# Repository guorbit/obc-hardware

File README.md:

# STM32-based Onboard Computer

This repository contains the KiCad project files and fabrication outputs of GU Orbit's new generation STM32F4-based OBC board.

Revision A of this board will fly on the CloudView-2 high altitude balloon mission. This revision is an 100% COTS design with no space grade parts.

## Documentation

### User Manual

Available [HERE](https://gla.sharepoint.com/:w:/s/GUorbit/EWbB4_OCiA1IiK20_8yILmEBxFCxNbRzXe-6b-aP8d8sqQ?e=ERlZXE) (University of Glasgow login required)

### Schematic Diagram

Available [HERE](https://gla.sharepoint.com/:b:/s/GUorbit/EcqzIoVTQb1NrapEKPAgqEgBkPuZpGcCXpksztv5thLR0g?e=U3XVNj) (University of Glasgow login required)

### Mechanical Drawing

Available [HERE](https://gla.sharepoint.com/:b:/s/GUorbit/EUr8ayuSMrpKpmlO9UEF-kwB01D8GUk2koGHjnPf7s4Tdw?e=q49YmD) (University of Glasgow login required)

### 3D Model for CAD

Available under the [CAD](/CAD) directory in STEP and FreeCAD formats

## Next Revision TODOs

- [ ] Replace HSE, LSE crystals with TCXO for precision
- [ ] Use another LTC4411 to protect the SWD port

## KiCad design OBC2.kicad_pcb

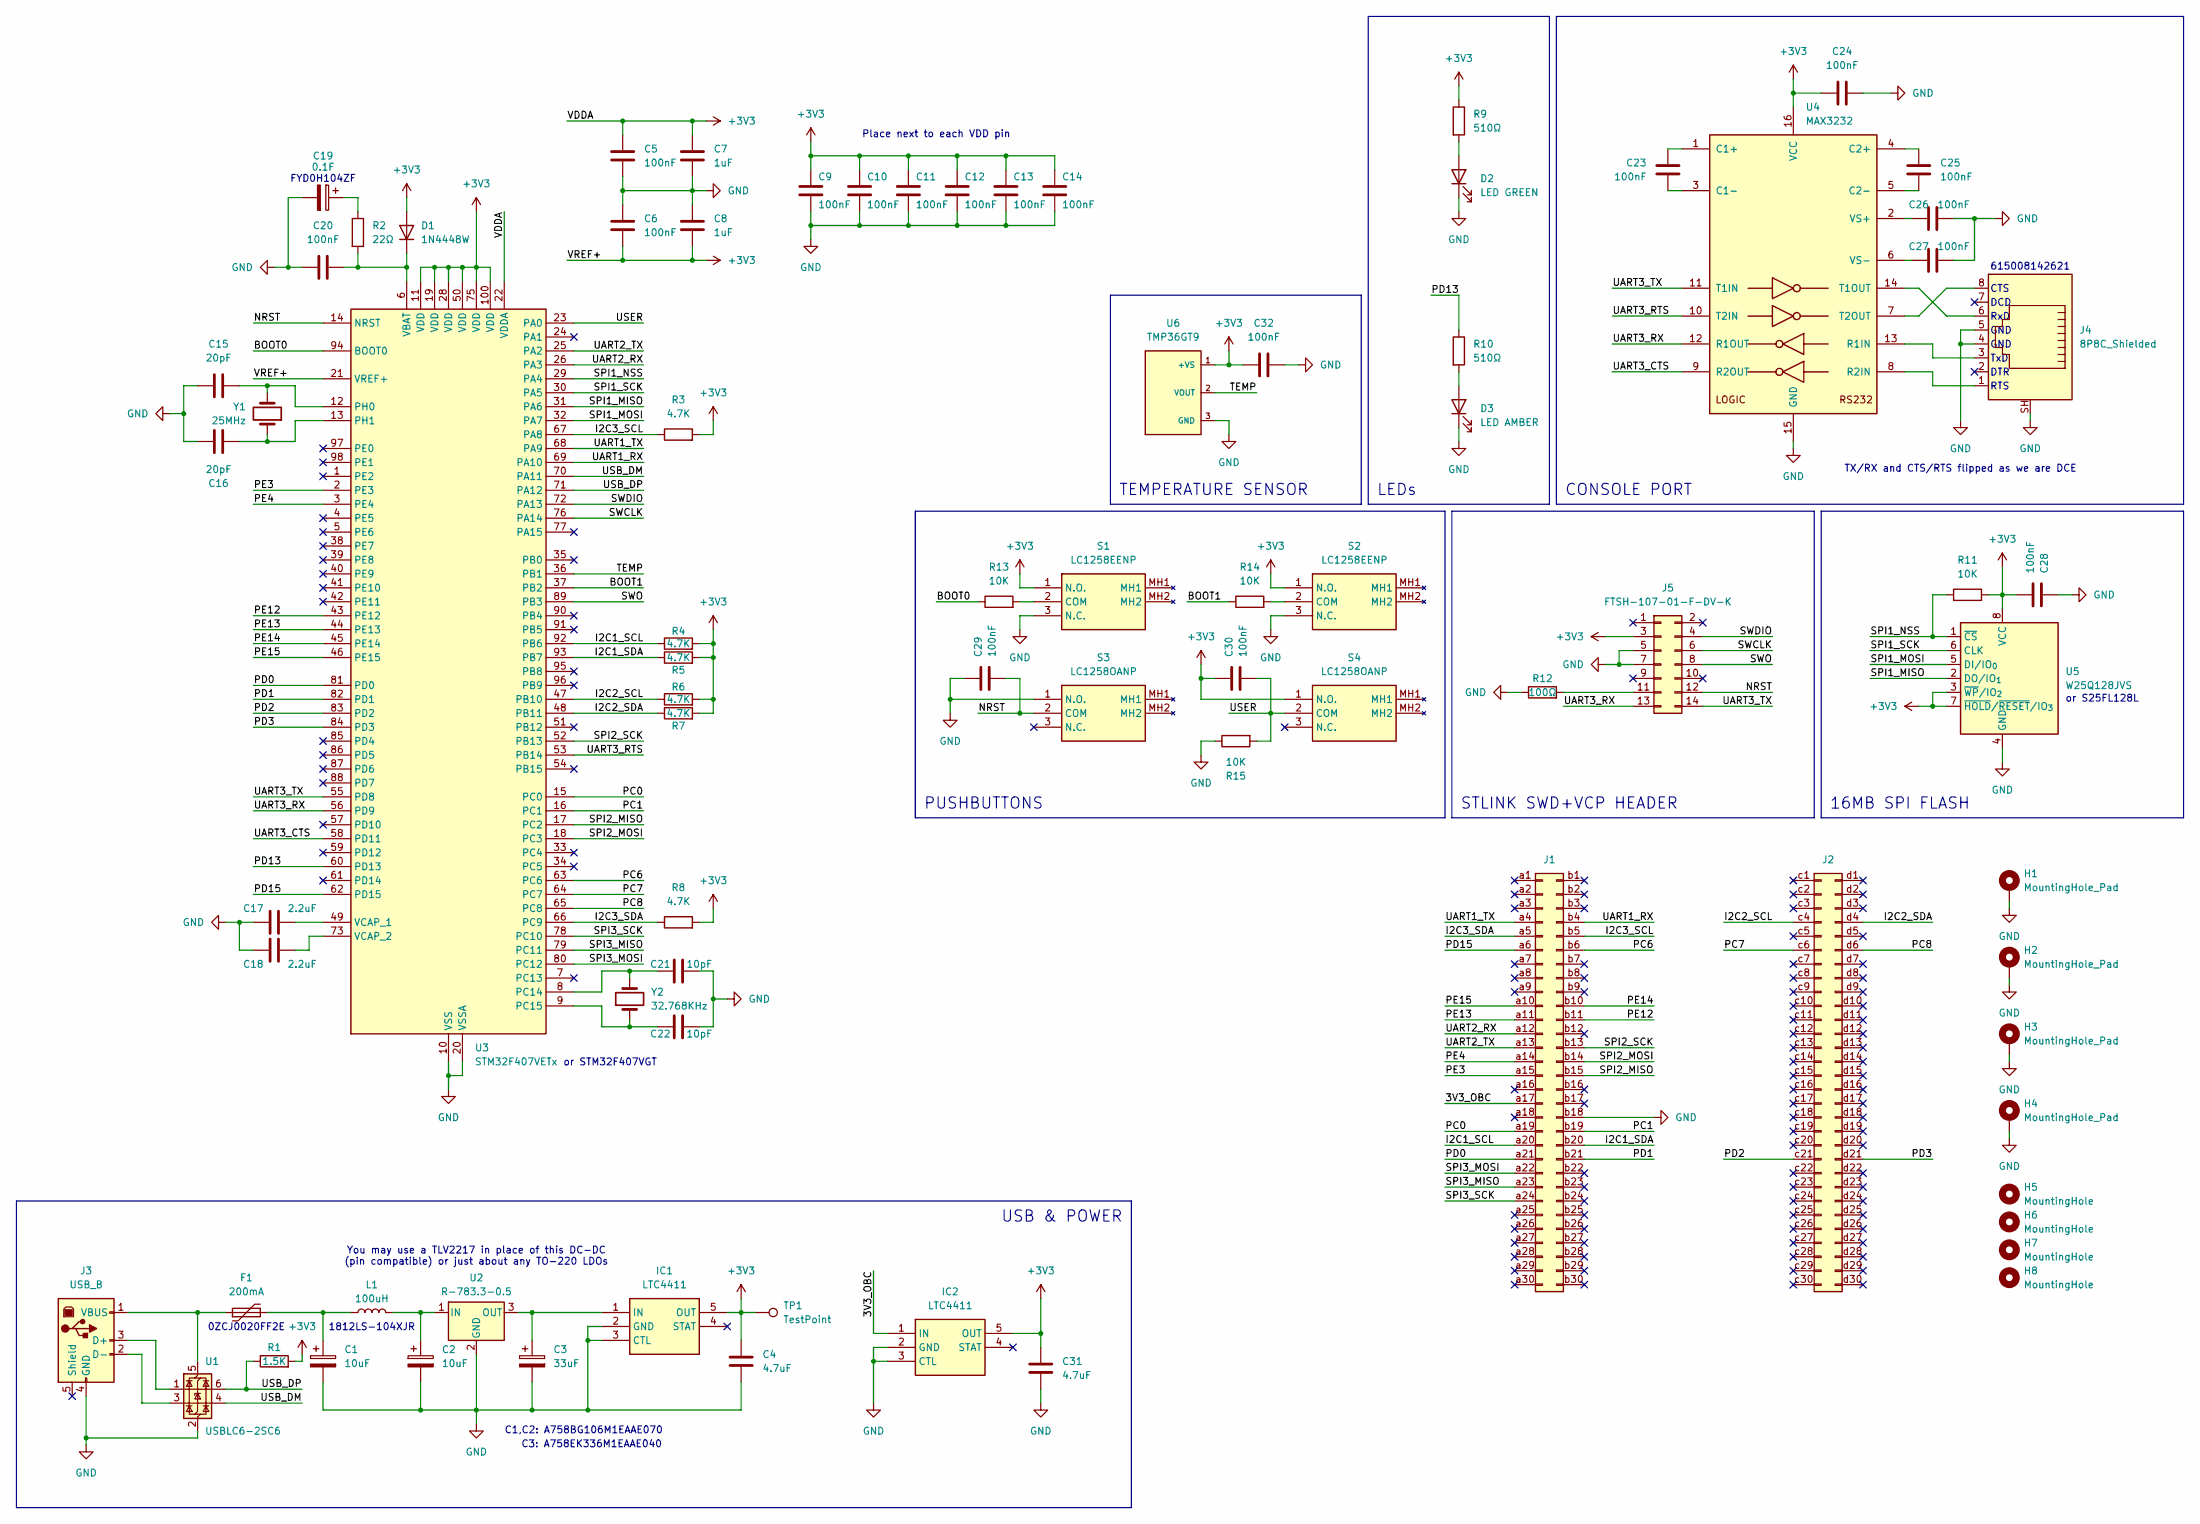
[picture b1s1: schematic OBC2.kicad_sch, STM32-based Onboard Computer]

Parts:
C1, C2: 10uF; CP_Radial_D5.0mm_P2.00mm
C3: 33uF; CP_Radial_D6.3mm_P2.50mm
C4, C31: 4.7uF; C_1206_3216Metric
C5, C6, C9, C10, C11, C12, C13, C14, C20, C23, C24, C25, C26, C27, C28, C29, C30, C32: 100nF; C_1206_3216Metric
C7, C8: 1uF; C_1206_3216Metric
C15, C16: 20pF; C_1206_3216Metric
C17, C18: 2.2uF; C_1206_3216Metric
C19: 0.1F; CP_Radial_D13.0mm_P5.00mm
C21, C22: 10pF; C_1206_3216Metric
D1: 1N4448W; D_SOD-123
D2: LED GREEN; LED_D5.0mm_Horizontal_O3.81mm_Z3.0mm
D3: LED AMBER; LED_D5.0mm_Horizontal_O3.81mm_Z3.0mm
F1: 200mA; Fuse_1206_3216Metric
H1, H2, H3, H4: MountingHole_Pad; MountingHole_3.2mm_M3_Pad_TopBottom
H5, H6, H7, H8: MountingHole; MountingHole_2mm
IC1, IC2: LTC4411; TSOT-23-5; Manufacturer_Part_Number LTC4411ES5#TRMPBF
J1, J2: Conn_02x30_Row_Letter_First; PinSocket_2x30_P2.00mm_Vertical
J3: USB_B; USB_B_Lumberg_2411_02_Horizontal
J4: 8P8C_Shielded; RJ45_Wuerth_7499010001A_Horizontal
J5: FTSH-107-01-F-DV-K; PinHeader_2x07_P1.27mm_Vertical_SMD
L1: 100uH; L_1812_4532Metric
R1: 1.5K; R_1206_3216Metric
R2: 22Ω; R_1206_3216Metric
R3, R4, R5, R6, R7, R8: 4.7K; R_1206_3216Metric
R9, R10: 510Ω; R_1206_3216Metric
R11, R13, R14, R15: 10K; R_1206_3216Metric
R12: 100Ω; R_1206_3216Metric
S1, S2: LC1258EENP; Manufacturer_Part_Number LC1258EENP; Mouser Part Number 612-LC1258EENP
S3, S4: LC1258OANP; Manufacturer_Part_Number LC1258OANP; Mouser Part Number 612-LC1258OANP
TP1: TestPoint; TestPoint_Loop_D2.60mm_Drill1.6mm_Beaded
U1: USBLC6-2SC6; SOT-23-6
U2: R-783.3-0.5; Converter_DCDC_RECOM_R-78E-0.5_THT
U3: STM32F407VETx; LQFP-100_14x14mm_P0.5mm
U4: MAX3232; SOIC-16_3.9x9.9mm_P1.27mm
U5: W25Q128JVS; SOIC-8_5.3x5.3mm_P1.27mm
U6: TMP36GT9; TO-92_Inline; PARTREV H
Y1: 25MHz; Crystal_SMD_HC49-SD
Y2: 32.768KHz; Crystal_C38-LF_D3.0mm_L8.0mm_Horizontal

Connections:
+3V3: C4.2, C5.2, C6.1, C7.2, C8.1, C9.2, C10.2, C11.2, C12.2, C13.2, C14.2, C24.1, C28.1, C30.1, C31.2, C32.1, D1.2 (A), IC1.5 (OUT), IC2.5 (OUT), J5.3, R1.2, R3.2, R4.2, R5.2, R6.2, R7.2, R8.2, R9.1, R11.2, S1.1 (N.O.), S2.1 (N.O.), S4.1 (N.O.), TP1.1, U3.11 (VDD), U3.19 (VDD), U3.21 (VREF+), U3.22 (VDDA), U3.28 (VDD), U3.50 (VDD), U3.75 (VDD), U3.100 (VDD), U4.16 (VCC), U5.3 (~WP/IO_{2}), U5.7 (~HOLD/~RESET/IO_{3}), U5.8 (VCC), U6.1 (+VS)
/3V3_OBC: IC2.1 (IN), J1.a17
/BOOT0: R13.1, U3.94 (BOOT0)
/BOOT1: R14.1, U3.37 (PB2)
/I2C1_SCL: J1.a20, R4.1, U3.92 (PB6)
/I2C1_SDA: J1.b20, R5.1, U3.93 (PB7)
/I2C2_SCL: J2.c4 (Pin_a4), R6.1, U3.47 (PB10)
/I2C2_SDA: J2.d4 (Pin_b4), R7.1, U3.48 (PB11)
/I2C3_SCL: J1.b5, R3.1, U3.67 (PA8)
/I2C3_SDA: J1.a5, R8.1, U3.66 (PC9)
/NRST: C29.2, J5.12, S3.2 (COM), U3.14 (NRST)
/PC0: J1.a19, U3.15 (PC0)
/PC1: J1.b19, U3.16 (PC1)
/PC6: J1.b6, U3.63 (PC6)
/PC7: J2.c6 (Pin_a6), U3.64 (PC7)
/PC8: J2.d6 (Pin_b6), U3.65 (PC8)
/PD0: J1.a21, U3.81 (PD0)
/PD1: J1.b21, U3.82 (PD1)
/PD2: J2.c21 (Pin_a21), U3.83 (PD2)
/PD3: J2.d21 (Pin_b21), U3.84 (PD3)
/PD13: R10.1, U3.60 (PD13)
/PD15: J1.a6, U3.62 (PD15)
/PE3: J1.a15, U3.2 (PE3)
/PE4: J1.a14, U3.3 (PE4)
/PE12: J1.b11, U3.43 (PE12)
/PE13: J1.a11, U3.44 (PE13)
/PE14: J1.b10, U3.45 (PE14)
/PE15: J1.a10, U3.46 (PE15)
/SPI1_MISO: U3.31 (PA6), U5.2 (DO/IO_{1})
/SPI1_MOSI: U3.32 (PA7), U5.5 (DI/IO_{0})
/SPI1_NSS: R11.1, U3.29 (PA4), U5.1 (~CS)
/SPI1_SCK: U3.30 (PA5), U5.6 (CLK)
/SPI2_MISO: J1.b15, U3.17 (PC2)
/SPI2_MOSI: J1.b14, U3.18 (PC3)
/SPI2_SCK: J1.b13, U3.52 (PB13)
/SPI3_MISO: J1.a23, U3.79 (PC11)
/SPI3_MOSI: J1.a22, U3.80 (PC12)
/SPI3_SCK: J1.a24, U3.78 (PC10)
/SWCLK: J5.6, U3.76 (PA14)
/SWDIO: J5.4, U3.72 (PA13)
/SWO: J5.8, U3.89 (PB3)
/TEMP: U3.36 (PB1), U6.2 (VOUT)
/UART1_RX: J1.b4, U3.69 (PA10)
/UART1_TX: J1.a4, U3.68 (PA9)
/UART2_RX: J1.a12, U3.26 (PA3)
/UART2_TX: J1.a13, U3.25 (PA2)
/UART3_CTS: U3.58 (PD11), U4.9 (R2OUT)
/UART3_RTS: U3.53 (PB14), U4.10 (T2IN)
/UART3_RX: J5.13, U3.56 (PD9), U4.12 (R1OUT)
/UART3_TX: J5.14, U3.55 (PD8), U4.11 (T1IN)
/USB_DM: U1.4 (I/O2), U3.70 (PA11)
/USB_DP: R1.1, U1.6 (I/O1), U3.71 (PA12)
/USER: C30.2, R15.2, S4.2 (COM), U3.23 (PA0)
GND: C1.2, C2.2, C3.2, C4.1, C5.1, C6.2, C7.1, C8.2, C9.1, C10.1, C11.1, C12.1, C13.1, C14.1, C15.1, C16.1, C17.1, C18.1, C19.2, C20.1, C21.2, C22.2, C24.2, C26.1, C27.1, C28.2, C29.1, C31.1, C32.2, D2.1 (K), D3.1 (K), H1.1, H2.1, H3.1, H4.1, IC1.2 (GND), IC1.3 (CTL), IC2.2 (GND), IC2.3 (CTL), J1.b18, J3.4 (GND), J4.4, J4.5, J4.SH, J5.5, J5.7, R12.1, R15.1, S1.3 (N.C.), S2.3 (N.C.), S3.1 (N.O.), U1.2 (GND), U2.2 (GND), U3.10 (VSS), U3.20 (VSSA), U3.27 (VSS), U3.74 (VSS), U3.99 (VSS), U4.15 (GND), U5.4 (GND), U6.3 (GND)
unnamed: C1.1, F1.2, L1.1
unnamed: C19.1, R2.1
unnamed: C20.2, D1.1 (K), R2.2, U3.6 (VBAT)
unnamed: D2.2 (A), R9.2
unnamed: D3.2 (A), R10.2
unnamed: C3.1, IC1.1 (IN), U2.3 (OUT)
unnamed: J3.3 (D+), U1.1 (I/O1)
unnamed: J3.2 (D-), U1.3 (I/O2)
unnamed: F1.1, J3.1 (VBUS), U1.5 (VBUS)
unnamed: J5.11, R12.2
unnamed: R13.2, S1.2 (COM)
unnamed: R14.2, S2.2 (COM)
unnamed: C2.1, L1.2, U2.1 (IN)
unnamed: C21.1, U3.8 (PC14), Y2.2
unnamed: C22.1, U3.9 (PC15), Y2.1
unnamed: C15.2, U3.12 (PH0), Y1.2
unnamed: C16.2, U3.13 (PH1), Y1.1
unnamed: C17.2, U3.49 (VCAP_1)
unnamed: C18.2, U3.73 (VCAP_2)
unnamed: C23.2, U4.1 (C1+)
unnamed: C23.1, U4.3 (C1-)
unnamed: C25.2, U4.4 (C2+)
unnamed: C25.1, U4.5 (C2-)
unnamed: J4.3, U4.13 (R1IN)
unnamed: J4.1, U4.8 (R2IN)
unnamed: J4.6, U4.14 (T1OUT)
unnamed: J4.8, U4.7 (T2OUT)
unnamed: C26.2, U4.2 (VS+)
unnamed: C27.2, U4.6 (VS-)

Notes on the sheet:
GND
FYD0H104ZF
or S25FL128L
CTS
RTS
TxD
C3: A758EK336M1EAAE040
Place next to each VDD pin
RxD
C1,C2: A758BG106M1EAAE070
You may use a TLV2217 in place of this DC-DC (pin compatible) or just about any TO-220 LDOs
or STM32F407VGT
615008142621
0ZCJ0020FF2E
DTR
TX/RX and CTS/RTS flipped as we are DCE
1812LS-104XJR
DCD
PUSHBUTTONS
USB & POWER
STLINK SWD+VCP HEADER
CONSOLE PORT
LEDs
TEMPERATURE SENSOR
16MB SPI FLASH

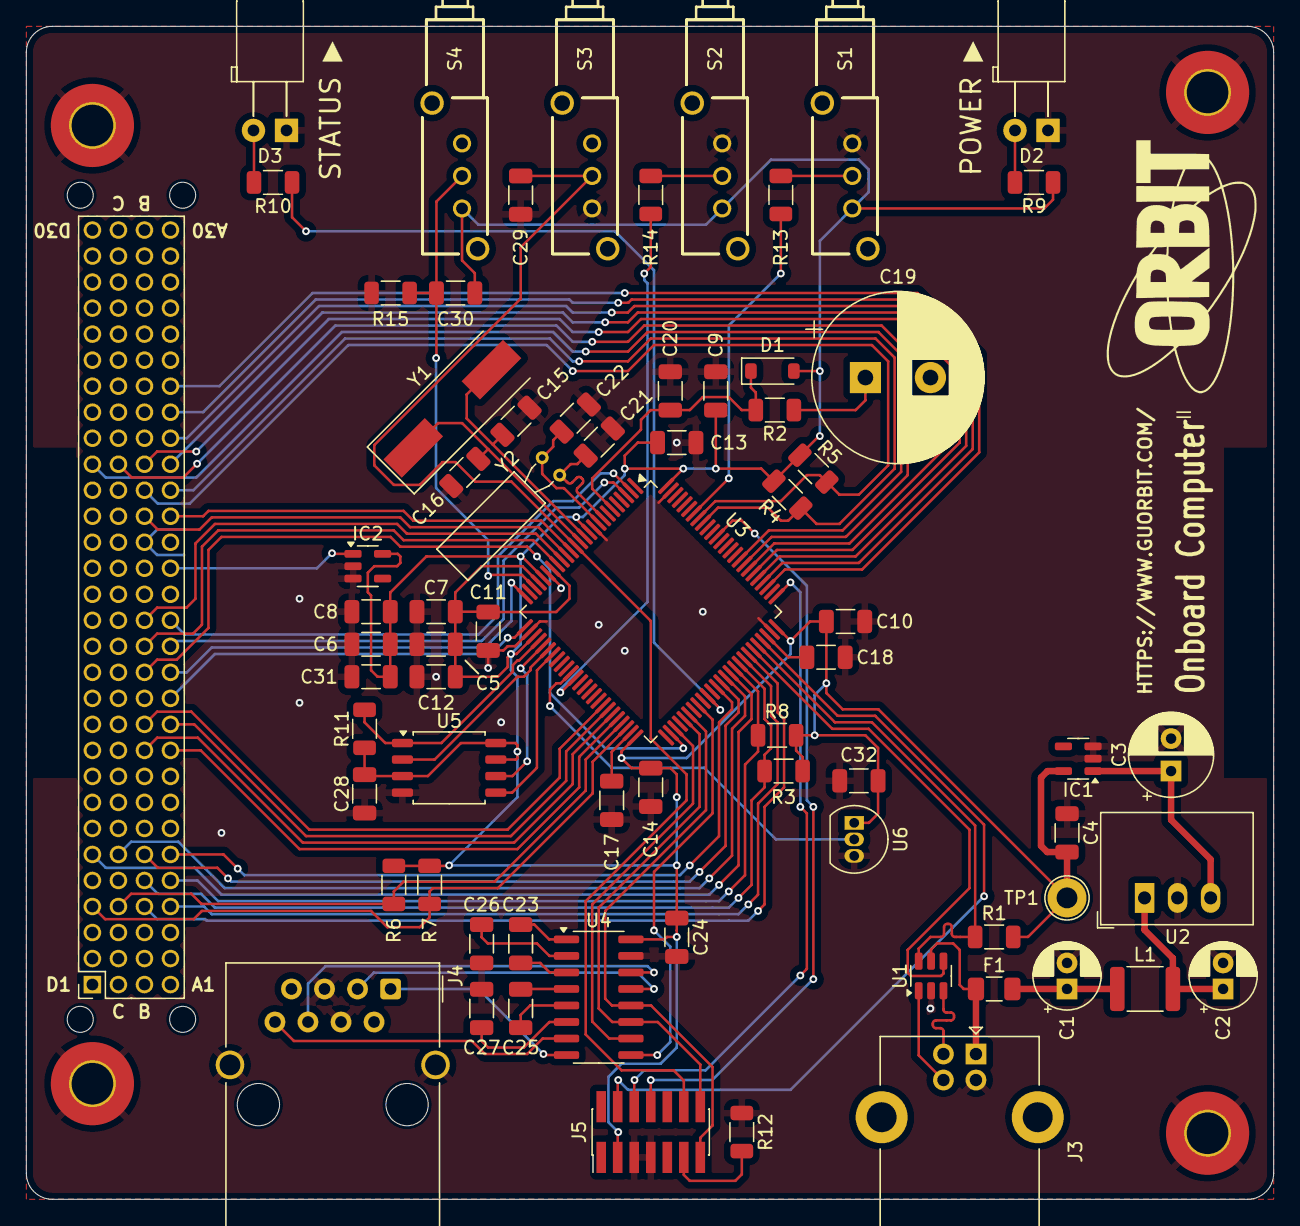
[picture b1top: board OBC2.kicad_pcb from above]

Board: 2 copper layers, 95.9 x 90.2 mm, 80 parts (0 on the bottom side), 83 nets.

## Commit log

2025-04-24 Revision A
2025-07-08 correct through-hole sizes
2025-07-10 next rev todos
2025-10-30 make the pcb bloo
2026-03-17 correct flipped i2c1 SCL SDA lines
